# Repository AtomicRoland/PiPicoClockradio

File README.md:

# PiPicoClockradio
A simple clock radio based on a Pi Pico, TM1637 display module and TDA5807 Stereo FM receiver.

# Installation                              
The first step is to install BBC Basic on the Pico, if you haven't already done 
so. The designers of the Pico have thought carefully about how you can provide 
the Pico with the program (firmware) you want to use as simply as possible. This 
can be a program with a specific task (such as my Electron Video card), but also 
an environment with a programming language such as Micro Python or of course BBC Basic.

There is a small white push button on the Pico to select the boot mode. If you 
turn on the Pico without pressing this button, it will start normally. However, 
if you press this button and then connect the Pico to your computer, it will be
shown as a USB drive in the Finder (Apple MacOS) or Explorer (Windows). All you 
have to do is drag the file with your program or firmware to the drive icon of the
Pi Pico. The file will then be copied to the Pico's flash memory and when finished,
the Pico will automatically reboot and start your program or firmware.

Let's do this step by step:
     • If the Pico is connected to your computer, disconnect it for a while.
     • In the file Explorer or Finder open the folder where 
       bbcbasic_console_rpico.uf2 is located.
     • Press the white button and connect the USB cable to your computer with your 
       other hand.
     • A new “drive” icon will now appear in the Finder or Explorer. This is 
       called RPI-RP2.
     • Drag and drop the uf2 file to this icon.
     • Wait a moment until the file has been copied and the Pico restarts 
       automatically.

During this restart, your computer may prompt you to unmount (eject) the media 
before removing it. Ignore this message, the file has been successfully copied 
and it can do no harm to remove the medium  without to eject it.
BBC Basic is now installed and ready to use.

The second step is to install the clock radio program. Step by step it goes as 
follows:
     • Open the clockradio.txt file in a text editor
     • Select the entire text and copy it to the clipboard
     • In BBC Basic type the command
        	NEW <enter>
     • Paste the text into the console window
     • When the text is pasted, press ESCAPE
     • Save the file with the name autorun.bbc

With these steps, the clock radio is ready to use. You can now start the program 
directly with the RUN statement. By using the name autorun.bbc the program will 
start automatically when the Pico is powered on or reset.

Have fun with it!

# License

The license for this Work (i.e. both the hardware and software) is simple:

1. You have the right to use the Work in any way you want for non-commercial use. Commercial use is considered when you integrate the Work into your own products or replicate the Work and sell it.

2. You may create your own hardware and software based on the Work for non-commercial use. However, for deviated projects you must use the same license.

# Warranties and Disclaimer

Except as required by law, the Work is licensed by the Licensor on an "as is" and "as available" basis and without any warranty of any kind, either express or implied.

# Limit of Liability

Subject to any liability which may not be excluded or limited by law the Licensor shall not be liable and hereby expressly excludes all liability for loss or damage howsoever and whenever caused to You.

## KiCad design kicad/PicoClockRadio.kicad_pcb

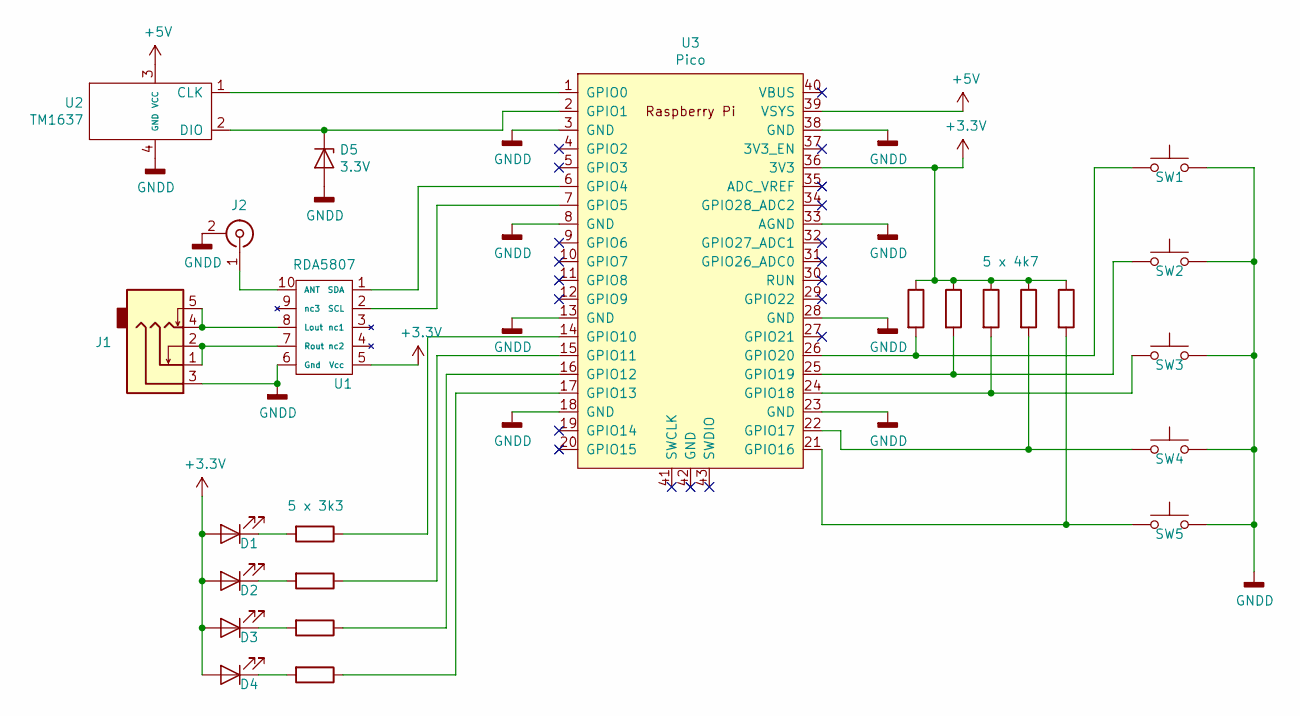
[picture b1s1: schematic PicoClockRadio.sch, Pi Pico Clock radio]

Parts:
D1, D2, D3, D4: LED; LED_D3.0mm
D5: 3.3V; D_A-405_P7.62mm_Horizontal
J1: AudioJack3_SwitchTR; 3.5mm audio stereo
J2: Conn_Coaxial; RCA connector
R1, R2, R3, R4, R7, R8, R9: R; R_Axial_DIN0207_L6.3mm_D2.5mm_P10.16mm_Horizontal
R5: 5 x 4k7; R_Axial_DIN0207_L6.3mm_D2.5mm_P10.16mm_Horizontal
R6: 5 x 3k3; R_Axial_DIN0207_L6.3mm_D2.5mm_P10.16mm_Horizontal
SW1, SW2, SW3, SW4, SW5: SW_Push; SW_PUSH-12mm
U1: RDA5807
U2: TM1637
U3: Pico; RPi_Pico_SMD_TH

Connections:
+3V3: D1.2 (A), D2.2 (A), D3.2 (A), D4.2 (A), R1.1, R2.1, R3.1, R4.1, R5.1, U1.5 (Vcc), U3.36 (3V3)
+5V: U2.3 (VCC), U3.39 (VSYS)
GNDD: D5.2 (A), J1.3, J2.2 (Ext), SW1.2, SW2.2, SW3.2, SW4.2, SW5.2, U1.6 (Gnd), U2.4 (GND), U3.3 (GND), U3.8 (GND), U3.13 (GND), U3.18 (GND), U3.23 (GND), U3.28 (GND), U3.33 (AGND), U3.38 (GND)
unnamed: D1.1 (K), R6.2
unnamed: D2.1 (K), R7.2
unnamed: D3.1 (K), R8.2
unnamed: D4.1 (K), R9.2
unnamed: D5.1 (K), U2.2 (DIO), U3.2 (GPIO1)
unnamed: J1.1, J1.2, U1.7 (Rout)
unnamed: J1.4, J1.5, U1.8 (Lout)
unnamed: J2.1 (In), U1.10 (ANT)
unnamed: R1.2, SW1.1, U3.26 (GPIO20)
unnamed: R2.2, SW2.1, U3.25 (GPIO19)
unnamed: R3.2, SW3.1, U3.24 (GPIO18)
unnamed: R4.2, SW4.1, U3.22 (GPIO17)
unnamed: R5.2, SW5.1, U3.21 (GPIO16)
unnamed: R6.1, U3.14 (GPIO10)
unnamed: R7.1, U3.15 (GPIO11)
unnamed: R8.1, U3.16 (GPIO12)
unnamed: R9.1, U3.17 (GPIO13)
unnamed: U1.1 (SDA), U3.6 (GPIO4)
unnamed: U1.2 (SCL), U3.7 (GPIO5)
unnamed: U2.1 (CLK), U3.1 (GPIO0)

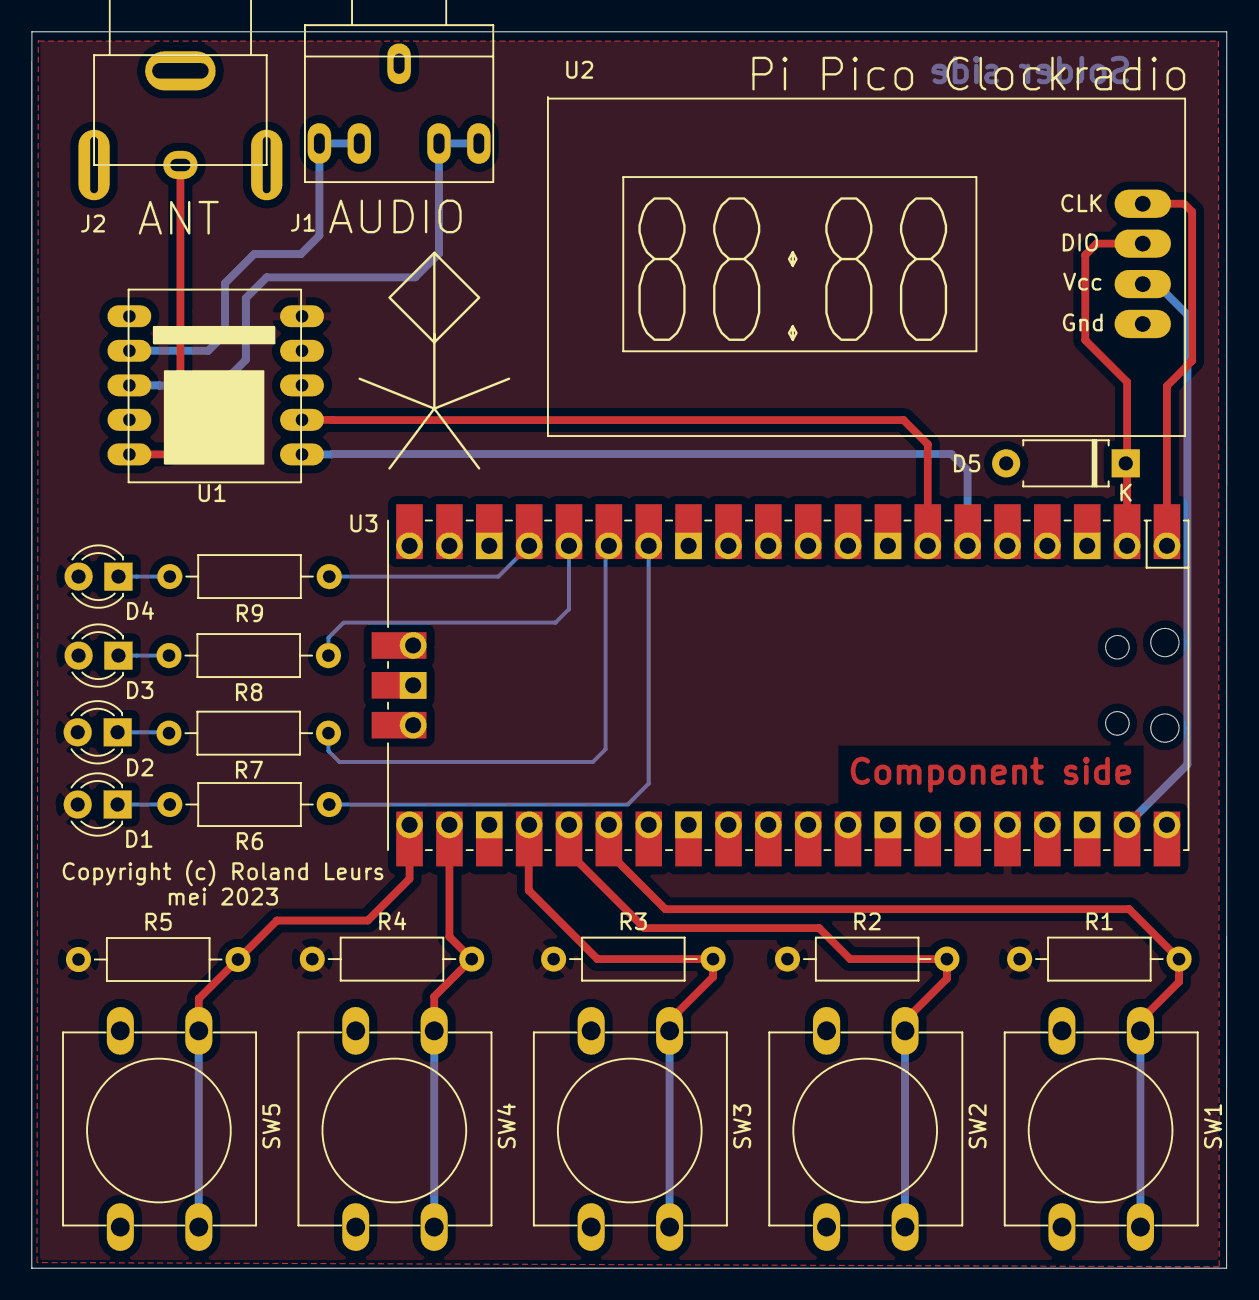
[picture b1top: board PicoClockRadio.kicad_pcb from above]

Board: 2 copper layers, 76.1 x 78.8 mm, 24 parts (0 on the bottom side), 23 nets.

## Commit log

2023-05-25 README.md
2023-05-25 Add files via upload
    Initial upload to Github.
2023-11-19 Add files via upload
    Expanded clock radio with alarm
2023-11-19 Create clock-radio-with-alarm.md
    A user manual with operating instructions.
2026-06-09 Rename datasheet-display-module,pdf to datasheet-display-module.pdf
    Corrected type in filename

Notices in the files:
kicad/PicoClockRadio.kicad_pcb:
(c) 2023 Roland Leurs
Copyright (c) Roland Leurs
